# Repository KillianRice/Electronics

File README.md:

# Electronics

Electronic schematics and PCB layouts.

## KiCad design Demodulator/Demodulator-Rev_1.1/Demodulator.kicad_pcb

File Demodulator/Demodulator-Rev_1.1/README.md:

# Demodulator-Rev_1.1

Made by Roger Ding, 2015/07/12

Schematics and PCB layout for an analog demodulator (using the AD734).

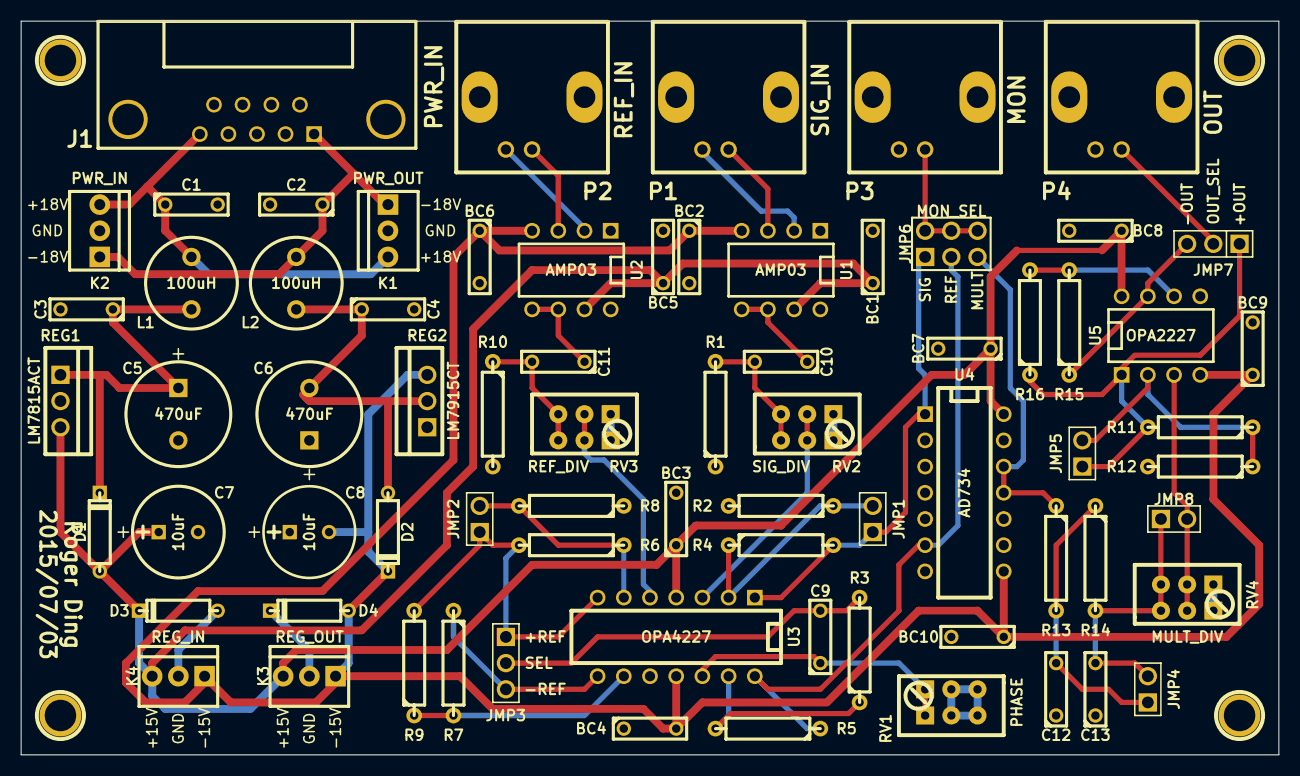
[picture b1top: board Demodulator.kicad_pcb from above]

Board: 2 copper layers, 121.9 x 71.1 mm, 77 parts (0 on the bottom side), 37 nets.

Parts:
1PIN1: MOUNT1; 1pin
1PIN2: MOUNT2; 1pin
1PIN3: MOUNT3; 1pin
1PIN4: MOUNT4; 1pin
BC1, BC2, BC3, BC4, BC5, BC6, BC7, BC8, BC9, BC10: 0.1uF; C2
C1, C2, C3, C4: 100nF; C2
C5, C6: 470uF; CP1
C7, C8: 10uF; C1.5V8V
C9, C10, C11, C12, C13: C; C2
D1, D2, D3, D4: 1N4002; D3
J1: PWR_IN; DB9M-L-Overhang
JMP1, JMP2, JMP4, JMP5, JMP8: BYPASS; PIN_ARRAY_2X1
JMP3: REF_INV; PIN_ARRAY_3X1
JMP6: DIL6; pin_array_3x2
JMP7: OUT_INV; PIN_ARRAY_3X1
K1: PWR_OUT; Molex-3pin
K2: PWR_IN; Molex-3pin
K3: REG_OUT; Molex-3pin
K4: REG_IN; Molex-3pin
L1, L2: 100uH; L1
P1: SIG_IN; BNC-L-Overhang
P2: REF_IN; BNC-L-Overhang
P3: MON; BNC-L-Overhang
P4: OUT; BNC-L-Overhang
R1, R2, R3, R4, R5, R6, R8, R10, R11, R12, R13, R14: R; R4
R7, R9: 50k; R4
R15, R16: 10k; R4
REG1: LM7815ACT; LM78xx-TO220
REG2: LM7915CT; LM79xx-TO220
RV1: PHASE; POT93
RV2: SIG_DIV; POT93
RV3: REF_DIV; POT93
RV4: MULT_DIV; POT93
U1, U2: AMP03; DIP-8__300
U3: OPA4227; DIP-14__300
U4: AD734; DIP-14__300
U5: OPA2227; DIP-8__300

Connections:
+15V: BC1.1, BC3.1, BC5.1, BC7.1, BC8.1, C7.1, D1.1, D3.2, K3.3, K4.3, REG1.3, U1.7, U2.7, U3.4, U4.14, U5.8
+18V: C1.1, J1.5, K1.3, K2.3, L1.1
+OUT: JMP5.1, JMP7.1, R11.2, R16.1, U5.1
+REF: JMP2.1, JMP3.1, R6.2, R9.2, U3.7
-15V: BC2.1, BC4.2, BC6.1, BC9.1, BC10.1, C8.2, D2.2, D4.1, K3.1, K4.1, REG2.3, U1.4, U2.4, U3.11, U4.8, U5.4
-18V: C2.1, J1.1, K1.1, K2.1, L2.1
-OUT: JMP7.3, R15.1, U5.7
-REF: JMP3.3, R7.1, U3.8
GND: BC1.2, BC2.2, BC3.2, BC4.1, BC5.2, BC6.2, BC7.2, BC8.2, BC9.2, BC10.2, C1.2, C2.2, C3.2, C4.2, C5.2, C6.1, C7.2, C8.1, C12.1, C13.1, D3.1, D4.2, J1.3, K1.2, K2.2, K3.2, K4.2, P3.2, P4.2, R1.1, R2.2, R8.1, R10.2, R12.2, REG1.2, REG2.1, RV1.2, RV1.3, RV2.1, RV3.1, RV4.1, U1.1, U2.1, U3.10, U4.2, U4.3, U4.4, U4.5, U4.7, U4.10, U5.5
MULT: JMP6.3, R13.1, U4.11, U4.12
unnamed: C10.1, U1.5, U1.6
unnamed: RV3.2, U3.5
unnamed: RV2.2, U3.3
unnamed: P1.2, U1.2
unnamed: C11.1, U2.5, U2.6
unnamed: P1.1, U1.3
unnamed: C9.1, RV1.1, U3.12
unnamed: R7.2, R9.1, U3.9
unnamed: R15.2, R16.2, U5.6
unnamed: C3.1, C5.1, D1.2, L1.2, REG1.1
unnamed: P2.1, U2.3
unnamed: P2.2, U2.2
unnamed: C4.1, C6.2, D2.1, L2.2, REG2.2
unnamed: C10.2, R1.2, RV2.3
unnamed: C11.2, R10.1, RV3.3
unnamed: JMP7.2, P4.1
unnamed: JMP8.2, RV4.2, U5.3
unnamed: JMP5.2, R11.1, R12.1, U5.2
unnamed: C12.2, JMP4.1, R13.2, R14.1
unnamed: R3.1, R5.2, U3.13
unnamed: C13.2, JMP4.2, JMP8.1, R14.2, RV4.3
unnamed: JMP1.2, R2.1, R4.1, U3.2
unnamed: JMP6.4, JMP6.5, JMP6.6, P3.1
unnamed: JMP2.2, R6.1, R8.2, U3.6
REF: JMP6.2, R5.1, U3.14, U4.6
REF_SEL: C9.2, JMP3.2, R3.2
SIG: JMP1.1, JMP6.1, R4.2, U3.1, U4.1

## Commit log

2016-07-12 Added power lock revision 2.0 Eagle .sch and .pcb files.
2016-07-12 Added Mathematica notebook for the Bode plot of the power lock circuit.
2016-07-12 Added a README for this folder. Also, the .sch and .pcb files were made with ExpressPCB, not Eagle.
2016-07-12 Updated the README.
2016-07-12 Added Digitally Controlled Switches Rev. 1.0.
2016-07-12 Added the analog demodulator circuit.
2016-07-12 Added README.md
2016-07-12 Temporarily removed demodulator circuit.
2016-07-12 Added demodulator schematic and PCB layout.
2016-07-12 Removed datasheet PDFs.
2016-07-12 Removed some larger files.
2016-07-12 Removed folder Dionysios locking circuit
2016-07-12 Removed the Resources folder.
2016-07-12 Removed Custom KiCAD 3D models
2016-07-12 Removed some KiCad backup files
2016-07-12 Added a KiCad .gitignore under the Demodulator-Rev1.1 folder
